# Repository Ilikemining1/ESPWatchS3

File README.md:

ESP32-S3 based Smartwatch Project
=================================

This project aims to develop an open-source smartwatch design based around an ESP32-S3 microcontroller, as it offers many useful features, such as integrated Wi-Fi, Bluetooth and 8MB of PSRAM.  This allows a watch to be designed with a minimal number of extra components beside the MCU itself.

Component Selection
-------------------

| Component | Model | Datasheet |
|-----------|-------|-----------|
| MCU | ESP32-S3R8 | [ESP32-S3](https://www.espressif.com/sites/default/files/documentation/esp32-s3_datasheet_en.pdf) |
| Display | CFAF240240A3-013TN  | [CFAF240240A3-013TN ](https://www.crystalfontz.com/products/document/4754/CFAF240240A3-013TNDatasheet.pdf) |
| Barometric Pressure Sensor | BMP390 | [BMP390](https://www.bosch-sensortec.com/media/boschsensortec/downloads/datasheets/bst-bmp390-ds002.pdf) |
| IMU | ICM-42688-P | [ICM-42688-P](https://invensense.tdk.com/wp-content/uploads/2022/12/DS-000347-ICM-42688-P-v1.7.pdf) |
| GNSS Receiver | MIA-M10Q-0 | [MIA-M10Q](https://content.u-blox.com/sites/default/files/documents/MIA-M10Q_DataSheet_UBX-22015849.pdf) |
| Flash | IS25LP128F-JKLE (16MB) | [IS25WP128](https://www.issi.com/WW/pdf/25LP-WP128F.pdf) |
| | | |
| Battery Charger | BQ24075RGTR | [BQ24075](https://www.ti.com/lit/ds/symlink/bq24075.pdf) |
| Fuel Gauge | BQ27441DRZR-G1A | [BQ27441-G1](https://www.ti.com/lit/ds/symlink/bq27441-g1.pdf) |
| Battery | ASR00007 | [ASR00007](https://www.mouser.com/datasheet/2/855/ASR00007_290mAh-3078659.pdf) |
| Battery Connector | SM02B-SRSS-TB(LF)(SN) | [SM02B-SRSS-TB(LF)(SN)](https://www.jst-mfg.com/product/pdf/eng/eSH.pdf) |
| | | |
| Main SMPS | TPS631000DRLR | [TPS631000](https://www.ti.com/lit/ds/symlink/tps631000.pdf) |
| LED Driver | AP3036B | [AP3036B](https://www.diodes.com/assets/Datasheets/AP3036B.pdf) |

ESP GPIO Allocation
-------------------
| GPIO | Function |
|------|----------|
| 0 | Bootloader (Strapping) FREE |
| 1 | I<sup>2</sup>C SDA |
| 2 | I<sup>2</sup>C SCL |
| 3 | JTAG Source Select (Strapping) FREE |
| 4 | Power Switch |
| 5 | User Switch 1 |
| 6 | User Switch 2 |
| 7 | User Switch 3 |
| 8 | Input Current 1 |
| 9 | Input Current 2 |
| 10 | LCD CS |
| 11 | LCD MOSI |
| 12 | LCD SCK |
| 13 | IMU INT1 |
| 14 | IMU INT2 |
| 15 | 32KHz XTAL |
| 16 | 32KHz XTAL |
| 17 | GNSS RX (UART 1 TX) |
| 18 | GNSS TX (UART 1 RX) |
| 19 | USB- |
| 20 | USB+ |
| 21 | Fuel Gauge Interrupt |
| 26 | |
| ... | Flash / PSRAM |
| 37 | |
| 38 | GNSS TX Ready |
| 39 | GNSS Timepulse |
| 40 | LCD DC |
| 41 | LCD Backlight |
| 42 | LCD TE |
| 43 | UART 0 TX |
| 44 | UART 0 RX |
| 45 | Flash Voltage Select (Strapping) FREE |
| 46 | ROM Messages (Strapping) FREE |
| 47 | SMPS Mode |
| 48 | SMPS Enable |

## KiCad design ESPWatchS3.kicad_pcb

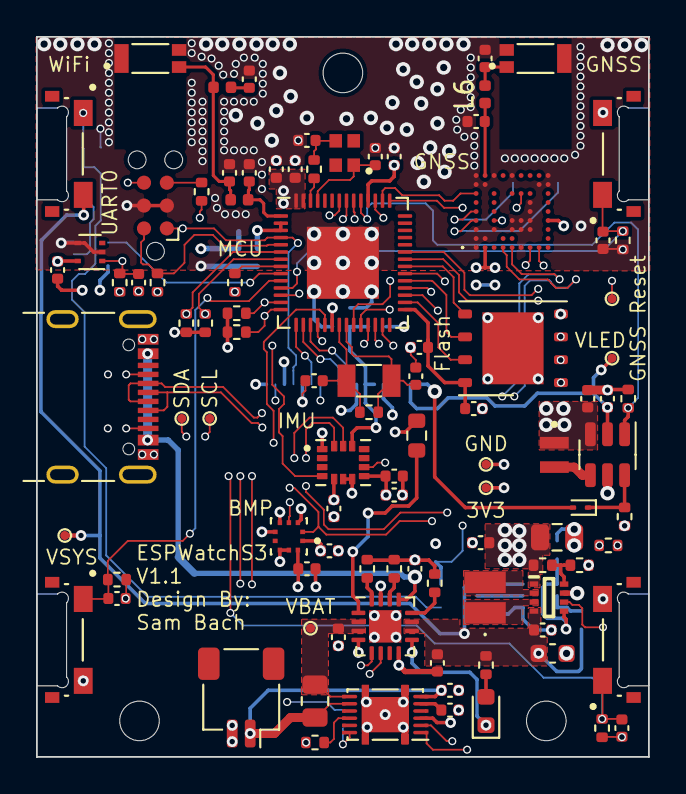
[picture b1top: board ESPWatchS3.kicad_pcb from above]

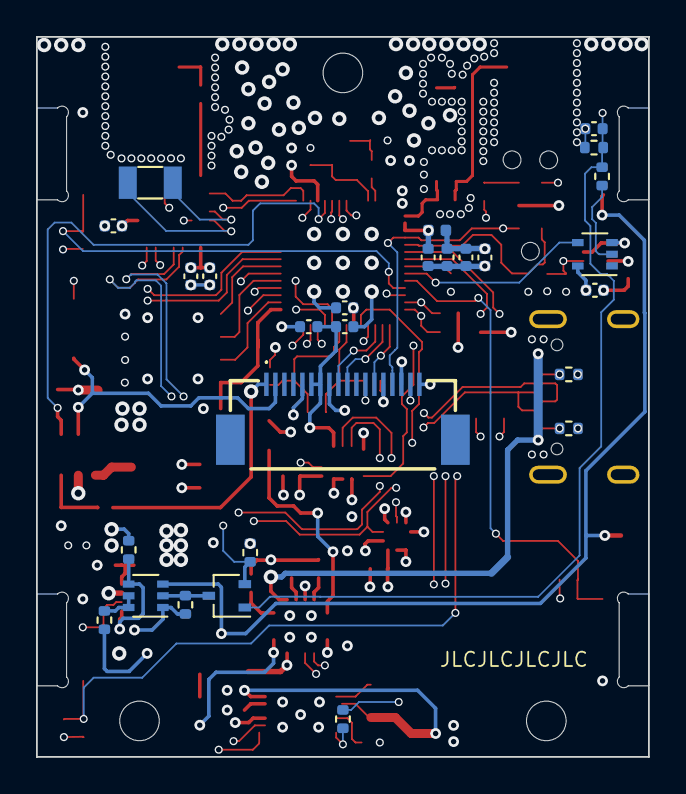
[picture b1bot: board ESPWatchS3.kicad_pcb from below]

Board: 6 copper layers, 34.0 x 40.0 mm, 126 parts (28 on the bottom side), 80 nets.

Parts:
ANT1: W3008C; ANTENNA_W3008C
ANT2: W3011A; ANTENNA_W3011A
BT1: ASR00007; JST_SH_SM02B-SRSS-TB_1x02-1MP_P1.00mm_Horizontal
C1: 47u; C_0805_2012Metric
C2: 22u; C_0603_1608Metric
C3, C4, C5, C6, C7, C8: 10u; C_0402_1005Metric
C9, C10, C11, C12, C13, C14, C15, C16: 1u; C_0402_1005Metric
C17, C18, C19, C20, C21, C22, C23, C24, C25, C26, C27, C28, C29, C30, C31, C32: 0.1u; C_0402_1005Metric
C33, C34, C35, C36, C37, C38: 0.01u; C_0402_1005Metric
C39, C40: 18p; C_0402_1005Metric
C41, C42: 10p; C_0402_1005Metric
C43: 4.8p; C_0402_1005Metric
C44: 3.9p; C_0402_1005Metric
C45, C46: DNF; C_0402_1005Metric
C47: 3.3p; C_0402_1005Metric
D1: Charge; LED_0603_1608Metric
D2: BAT54CW; SOT-323_SC-70
D3: CDSQR400B; D_SOD-923
H1, H2, H3: MountingHole; MountingHole_2.2mm_M2
J1: USB; USB_C_Receptacle_GCT_USB4105-xx-A_16P_TopMnt_Horizontal
J2: LCD; CS050Z18GA0
J3: UART0; Tag-Connect_TC2030-IDC-NL_2x03_P1.27mm_Vertical
L1: 1u; SRP2512TMA1R0M
L2: 22u; IND_VLS201612CX-220M-1
L3: DNF; L_0402_1005Metric
L4: 1.8n; L_0402_1005Metric
L5: 2.2n; L_0402_1005Metric
L6: 0R; L_0402_1005Metric
Q1: DMC2710UDW; SOT-363_SC-70-6
R1: 511k; R_0402_1005Metric
R2, R3, R4, R5, R6, R7, R8, R9, R10, R11, R12, R13, R14, R15: 100k; R_0402_1005Metric
R16: 91k; R_0402_1005Metric
R17, R18, R19, R20: 10k; R_0402_1005Metric
R21: 6.2k; R_0402_1005Metric
R22, R23: 5.1k; R_0402_1005Metric
R24, R25: 2.2k; R_0402_1005Metric
R26, R32: DNF; R_0402_1005Metric
R27: 1.6k; R_0402_1005Metric
R28, R29: 470R; R_0402_1005Metric
R30: 10R; R_0402_1005Metric
R31: 10m; R_0805_2012Metric
R33: 20nH; R_0402_1005Metric
S1, S2, S3, S4: EVQ-P4HB3B; SW_EVQ-P4HB3B
TH1: 10k; R_0603_1608Metric
TP1: GND; TestPoint_Pad_D0.5mm
TP2: VBAT; TestPoint_Pad_D0.5mm
TP3: SDA; TestPoint_Pad_D0.5mm
TP4: SCL; TestPoint_Pad_D0.5mm
TP5: VSYS; TestPoint_Pad_D0.5mm
TP6: 3V3; TestPoint_Pad_D0.5mm
TP7: GNSS Reset; TestPoint_Pad_D0.5mm
TP8: VLED; TestPoint_Pad_D0.5mm
U1: ESP32-S3R8; QFN-56-1EP_7x7mm_P0.4mm_EP4x4mm
U2: IS25LP128F-JKLE; WSON-8-1EP_6x5mm_P1.27mm_EP3.4x4mm
U3: MIA-M10Q-00B; MIAM10Q00B
U4: ICM-42688-P; PQFN50P300X250X97-14N
U5: BMP390; XDCR_BMP390
U6: BQ24075RGTR; VQFN-16-1EP_3x3mm_P0.5mm_EP1.8x1.8mm
U7: BQ27441-G1A; Texas_S-PDSO-N12
U8: TPS631000DRLR; SOTFL50P160X60-8N
U9: BD48xxFVE; VSOF5
U10: SN74LV1T34DCK; SOT-353_SC-70-5
U11: AP3036B; SOT-23-6
Y1: 40MHz; OSC_XRCGB40M000F1S1DR0
Y2, Y3: 32.768kHz; Crystal_SMD_3215-2Pin_3.2x1.5mm

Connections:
+3V3: C1.1, C4.1, C6.1, C7.1, C8.1, C12.1, C14.1, C15.1, C17.1, C19.1, C20.1, C21.1, C24.1, C25.1, C26.1, C27.1, C28.1, C29.1, C30.1, C31.1, C32.1, C34.1, J2.6, J2.7, J2.16, L2.1, L5.2, R1.1, R7.1, R14.2, R15.2, R17.1, R19.1, R24.1, R25.1, S2.2, S3.2, S4.2, TP6.1, U1.20 (VDD3P3_RTC), U1.46 (VDD3P3_CPU), U1.55 (VDDA1), U1.56 (VDDA2), U3.B1 (VCC), U3.J4 (V_IO), U4.1 (AP_AD0), U4.5 (VDDIO), U4.8 (VDD), U4.12 (AP_CS), U5.1 (VDDIO), U5.6 (CSB), U5.10 (VDD), U8.1 (VOUT), U9.5 (VDD), U10.5 (VCC), U11.3 (VIN)
+SYS: C2.1, C5.1, C23.1, Q1.3 (S), R9.1, R28.2, S1.2, TP5.1, U6.10 (OUT), U6.11 (OUT), U8.4 (VIN)
/CHG_EN1: R2.1, U1.13 (GPIO8), U6.6 (EN1)
/CHG_EN2: R3.1, U1.14 (GPIO9), U6.5 (EN2)
/D+: J1.A6 (D+), J1.B6 (D+), U1.26 (GPIO20)
/D-: J1.A7 (D-), J1.B7 (D-), U1.25 (GPIO19)
/ESP_BOOT: J3.2, R14.1, U1.5 (GPIO0)
/ESP_RESET: C33.1, J2.15, J3.1, R17.2, U1.4 (CHIP_PU), U9.1 (VOUT)
/FUEL_GPO: R19.2, U1.27 (GPIO21), U7.12 (GPOUT)
/GNSS_RX: U1.23 (GPIO17), U3.H1 (RX)
/GNSS_TP: U1.44 (MTCK), U3.A7 (TIMEPULSE)
/GNSS_TX: U1.24 (GPIO18), U3.G1 (TX)
/GNSS_TXRDY: U1.43 (GPIO38), U3.F7 (PIO6)
/IMU_INT1: U1.18 (GPIO13), U4.4 (INT1)
/IMU_INT2: U1.19 (GPIO14), U4.9 (INT2)
/LCD_BL: R13.1, U1.47 (MTDI), U11.1 (CTRL)
/LCD_CS: J2.13, U1.15 (GPIO10)
/LCD_DC: J2.12, U1.45 (MTDO)
/LCD_MOSI: J2.10, U1.16 (GPIO11)
/LCD_SCK: J2.9, U1.17 (GPIO12)
/LCD_TE: J2.17, U1.48 (MTMS)
/PWR_BTN: U1.9 (GPIO4), U10.4 (Y)
/SCL: R25.2, TP4.1, U1.7 (GPIO2), U3.E1 (SCL), U4.13 (AP_SCL), U5.2 (SCK), U7.2 (SCL)
/SDA: R24.2, TP3.1, U1.6 (GPIO1), U3.D1 (SDA), U4.14 (AP_SDA), U5.4 (MOSI/SDA), U7.1 (SDA)
/SMPS_EN1: D2.2, R7.2, U1.36 (SPICLK_N)
/SMPS_EN2: Q1.4 (D), R5.1, U8.5 (EN)
/SMPS_MODE: R6.1, U1.37 (SPICLK_P), U8.6 (MODE)
/USB_VBUS: C13.1, J1.A4 (VBUS), J1.A9 (VBUS), J1.B4 (VBUS), J1.B9 (VBUS), U6.13 (IN)
/USER_BTN1: C38.2, R12.1, S2.1, U1.10 (GPIO5)
/USER_BTN2: C36.2, R10.1, S3.1, U1.11 (GPIO6)
/USER_BTN3: C37.2, R11.1, S4.1, U1.12 (GPIO7)
/VDD_SPI: C9.1, C18.1, U1.29 (VDD_SPI), U2.8 (VCC)
BAT: C3.1, R31.1, TP2.1, U6.2 (BAT), U6.3 (BAT), U7.7 (SRN)
GND: ANT1.G1, ANT1.G2, ANT2.G1, ANT2.G2, BT1.2 (-), C1.2, C2.2, C3.2, C4.2, C5.2, C6.2, C7.2, C8.2, C9.2, C10.2, C11.2, C12.2, C13.2, C14.2, C15.2, C16.2, C17.2, C18.2, C19.2, C20.2, C21.2, C22.2, C23.2, C24.2, C25.2, C26.2, C27.2, C28.2, C29.2, C30.2, C31.2, C32.2, C33.2, C34.2, C35.1, C36.1, C37.1, C38.1, C39.2, C40.2, C41.2, C42.2, C43.2, C44.2, C45.2, C46.2, C47.2, J1.A1 (GND), J1.A12 (GND), J1.B1 (GND), J1.B12 (GND), J2.5, J2.8, J2.14, J2.18, J3.3, J3.4, Q1.1 (S), R2.2, R3.2, R4.2, R5.2, R6.2, R8.2, R10.2, R11.2, R12.2, R13.2, R16.2, R18.2, R21.2, R22.2, R23.2, R26.2, R27.2, R30.2, TH1.2, TP1.1, U1.57 (GND), U2.4 (GND), U2.9 (EP), U3.A1 (GND), U3.A2 (GND), U3.A3 (GND), U3.A8 (GND), U3.A9 (GND), U3.B2 (GND), U3.B8 (GND), U3.C3 (GND), U3.C9 (GND), U3.E3 (GND), U3.E4 (GND), U3.E9 (GND), U3.F1 (GND), U3.F3 (GND), U3.F4 (GND), U3.G3 (GND), U3.G4 (GND), U3.G5 (GND), U3.G6 (GND), U3.H8 (GND), U3.J8 (GND), U3.J9 (GND), U4.6 (GND), U4.7 (RESV), U5.3 (VSS), U5.5 (MISO/SA0), U5.8 (VSS), U5.9 (VSS), U6.4 (~CE), U6.8 (VSS), U6.15 (SYSOFF), U6.17 (EP), U7.3 (VSS), U7.13 (EP), U8.7 (GND), U9.2 (GND), U9.4 (GND), U10.3 (GND), U11.5 (GND)
unnamed: ANT1.FEED, C44.1, L3.2, L4.1
unnamed: ANT2.FEED, C47.1, L6.2
unnamed: BT1.1 (+), C10.1, R31.2, U7.6 (BAT), U7.8 (SRP)
unnamed: C22.1, L5.1, U1.2 (VDD3P3), U1.3 (VDD3P3)
unnamed: C35.2, D2.1, R4.1, R20.1, S1.1
unnamed: C39.1, R33.1, Y1.3
unnamed: C45.1, L3.1
unnamed: D1.2 (A), R28.1
unnamed: D1.1 (K), U6.9 (~CHG)
unnamed: D3.2 (A), J2.1
unnamed: D3.1 (K), R30.1, U11.6 (FB)
unnamed: J1.A5 (CC1), R23.1
unnamed: J1.B5 (CC2), R22.1
unnamed: C16.1, J2.2, TP8.1, U11.2 (VOUT)
unnamed: J3.5, R29.2
unnamed: J3.6, U1.50 (U0RXD)
unnamed: Q1.5 (G), Q1.6 (D), R9.2
unnamed: D2.3, Q1.2 (G), R8.1
unnamed: R15.1, U1.8 (GPIO3)
unnamed: C43.1, L4.2, U1.1 (LNA_IN)
unnamed: U1.33 (SPICLK), U2.6 (SCK)
unnamed: U1.32 (SPICS0), U2.1 (~CE)
unnamed: U1.35 (SPID), U2.5 (SI/IO0)
unnamed: U1.30 (SPIHD), U2.7 (~HLD/IO3)
unnamed: U1.34 (SPIQ), U2.2 (SO/IO1)
unnamed: U1.31 (SPIWP), U2.3 (~WP/IO2)
unnamed: R29.1, U1.49 (U0TXD)
unnamed: C42.1, R32.2, U1.22 (XTAL_32K_N), Y2.1
unnamed: C41.1, R32.1, U1.21 (XTAL_32K_P), Y2.2
unnamed: C40.1, U1.53 (XTAL_N), Y1.1
unnamed: R33.2, U1.54 (XTAL_P)
unnamed: TP7.1, U3.C4 (RESET_N)
unnamed: C46.1, L6.1, U3.B9 (RF_IN)
unnamed: U3.A4 (RTC_I), Y3.2
unnamed: U3.A5 (RTC_O), Y3.1
unnamed: R27.1, U6.12 (ILIM)
unnamed: R21.1, U6.16 (ISET)
unnamed: R26.1, U6.14 (TMR)
unnamed: TH1.1, U6.1 (TS)
unnamed: R18.1, U7.10 (BIN)
unnamed: C11.1, U7.5 (VDD)
unnamed: R1.2, R16.1, U8.8 (FB)
unnamed: L1.1, U8.3 (LX1)
unnamed: L1.2, U8.2 (LX2)
unnamed: R20.2, U10.2 (A)
unnamed: L2.2, U11.4 (SW)

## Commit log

2023-04-20 Update gitignore
2023-04-20 Initial design file commit
2023-04-20 Add README
2023-04-20 Fix readme typos
2023-04-20 Initial schematic work
2023-04-21 Schematic work and component selection
2023-04-22 Schematic work, power supplies and GNSS stuff
2023-04-22 Update Schematic
2023-04-22 Update README info
2023-04-23 Pick fuel gauge and protection IC, implemented.
2023-04-23 Update README with charger selection
2023-04-23 Fix issues with readme
2023-04-23 Added connector for OLED, update README.
2023-04-23 Configured Strapping Pins
2023-04-23 Fixed Typo
2023-04-25 More schematic work, added buttons
2023-04-25 Update I2C Pinout
2023-04-25 Added buttons!
2023-04-25 Added Status LEDs, UART Debug
2023-04-25 Mostly finished schematic layout
2023-04-25 Initial annotation, and added OLED VDD Jumper
2023-04-25 Initial footprint assignments
2023-04-25 Finish part footprint assignment
2023-04-25 Partially fixed schematic symbols missing pins
2023-04-25 Initial PCB settings
2023-04-25 Fixed footprints, dumped parts into PCB layout
2023-04-25 Initial PCB Stuff
2023-04-26 PCB Layout
2023-04-27 PCB Work
2023-04-27 More changes
2023-04-28 More PCB Work
2023-05-19 Almost done PCB routing
2023-05-20 PCB Fully Routed
2023-05-20 Final PCB touches
2023-05-20 Add PCB Imagery
2023-05-23 Adjust OLED connections
2023-05-25 Final changes to design for V0.1
2023-05-25 Update README with switch away from coin cell.
2023-05-25 Fix README typo
2023-05-25 Cleanup for Rev 1.0
2023-05-25 Update schematic with V1.0 design
2023-05-26 Finish reannotation of schematic
2023-05-26 Initial PCB Generation
2023-05-26 Initial PCB work for V1.0
2023-05-29 Update schematic to add mounting holes
2023-06-08 Significant PCB work
2023-06-09 Even more!
2023-06-10 Even more
2023-06-12 Routing continues
2023-06-14 0 nets unrouted!
2023-07-08 Finished 40mm round PCB
2023-07-08 Update README to prep for changes in design
2023-07-08 Adjust readme to avoid conflict
2023-07-08 Schematic work
2023-07-08 Remove existing PCB layout
2023-07-09 Library and schematic cleanup, revised designwork
2023-07-10 Finish and reannotate schematic minus LCD BL SMPS
2023-07-10 Rethought pin allocation for power use
2023-07-10 Finalize schematic?
2023-07-11 Re-annotated schematic
2023-07-11 Finished Footprint Assignment
2023-07-12 Initial PCB Work
2023-07-14 Routing work
2023-07-14 Layout continues
2023-07-14 More of the same
2023-07-15 Just 50 nets left!
2023-07-16 Cleanup work, silkscreen, file exports
2023-07-18 Update production files
2023-07-18 Update Readme with LED driver info
2023-07-19 Update schematic value and reexport final gerbers
2023-08-23 Initial PCB V1.1 changes
2023-08-24 Initial code commit
2023-08-24 Patches to component libraries
2024-06-08 Removed old code from repository
